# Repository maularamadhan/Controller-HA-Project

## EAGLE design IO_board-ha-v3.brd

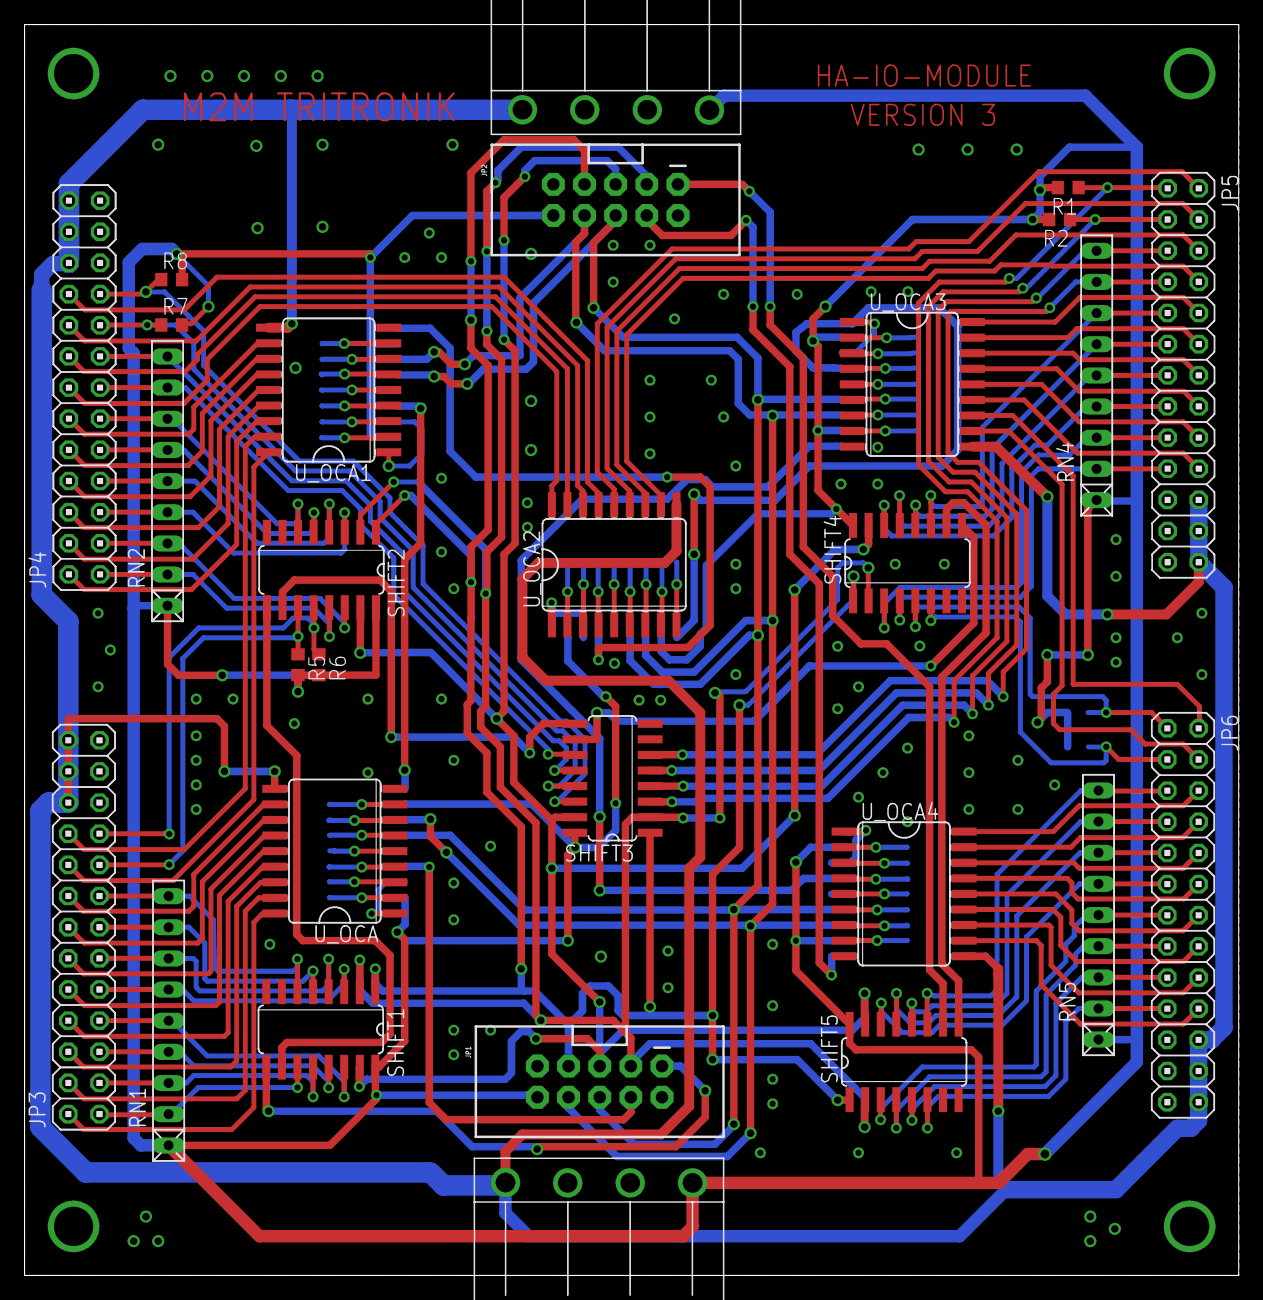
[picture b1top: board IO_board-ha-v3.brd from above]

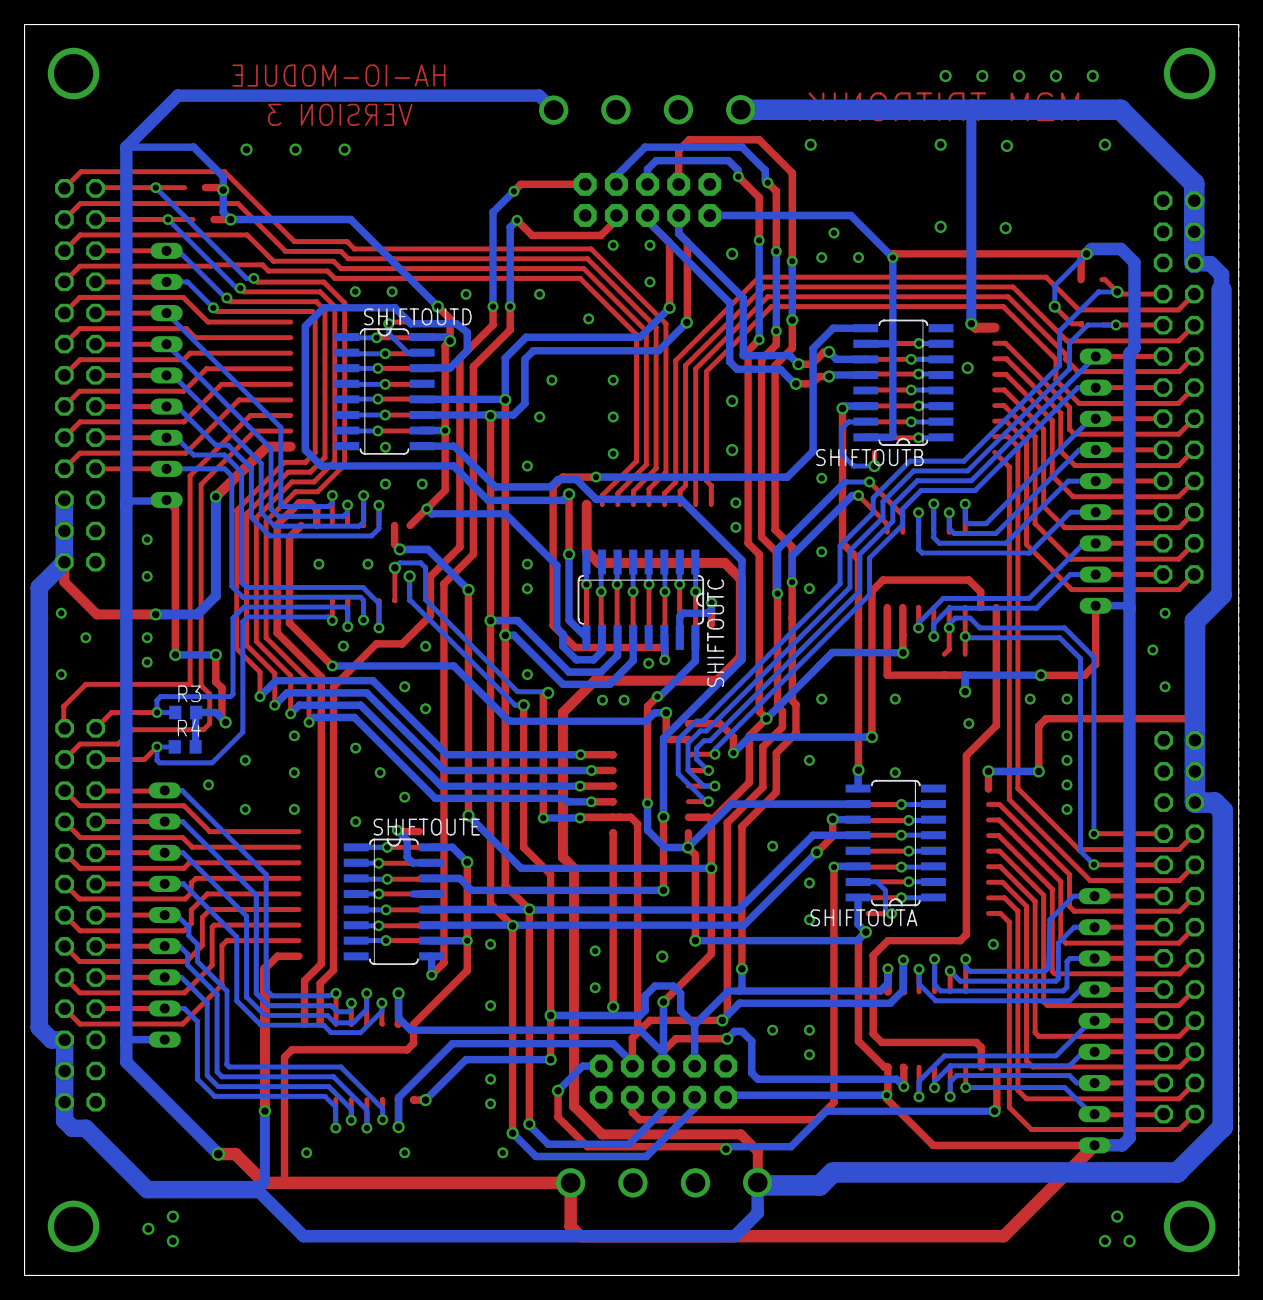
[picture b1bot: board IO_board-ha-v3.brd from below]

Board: 2 copper layers, 99.0 x 102.0 mm, 35 parts (7 on the bottom side), 140 nets.

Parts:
J1, J2: 4-PIN-CON-1759017
JP1, JP2: 2X5-SHROUDED
JP3, JP4, JP5, JP6: 2X13
R1, R2, R3, R4, R5, R6, R7, R8: 10K; R0603
RN1, RN2, RN4, RN5: 10K; RN-9
SHIFT1, SHIFT2, SHIFT3, SHIFT4, SHIFT5: 74HC165D; SO16
SHIFTOUTA: 74HC595D; SO16
SHIFTOUTB: 74HC595D; SO16
SHIFTOUTC: 74HC595D; SO16
SHIFTOUTD: 74HC595D; SO16
SHIFTOUTE: 74HC595D; SO16
U_OCA, U_OCA1, U_OCA2, U_OCA3, U_OCA4: ULN2803; SO18L

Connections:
1-1: JP3.1, RN1.2, SHIFT1.11
1-2: JP3.3, RN1.3, SHIFT1.12
1-3: JP3.5, RN1.4, SHIFT1.13
1-4: JP3.7, RN1.5, SHIFT1.14
1-5: JP3.9, RN1.6, SHIFT1.3
1-6: JP3.11, RN1.7, SHIFT1.4
1-7: JP3.13, RN1.8, SHIFT1.5
1-8: JP3.15, RN1.9, SHIFT1.6
2-1: JP3.17, R5.1, SHIFT2.11
2-2: JP3.19, R6.1, SHIFT2.12
2-3: JP4.1, RN2.2, SHIFT2.13
2-4: JP4.3, RN2.3, SHIFT2.14
2-5: JP4.5, RN2.4, SHIFT2.3
2-6: JP4.7, RN2.5, SHIFT2.4
2-7: JP4.9, RN2.6, SHIFT2.5
2-8: JP4.11, RN2.7, SHIFT2.6
3-1: JP4.13, RN2.8, SHIFT3.11
3-2: JP4.15, RN2.9, SHIFT3.12
3-3: JP4.17, R7.1, SHIFT3.13
3-4: JP4.19, R8.1, SHIFT3.14
3-5: JP5.1, R1.1, SHIFT3.3
3-6: JP5.3, R2.1, SHIFT3.4
3-7: JP5.5, RN4.9, SHIFT3.5
3-8: JP5.7, RN4.8, SHIFT3.6
4-1: JP5.9, RN4.7, SHIFT4.11
4-2: JP5.11, RN4.6, SHIFT4.12
4-3: JP5.13, RN4.5, SHIFT4.13
4-4: JP5.15, RN4.4, SHIFT4.14
4-5: JP5.17, RN4.3, SHIFT4.3
4-6: JP5.19, RN4.2, SHIFT4.4
4-7: JP6.1, R3.1, SHIFT4.5
4-8: JP6.3, R4.1, SHIFT4.6
5-1: JP6.5, RN5.9, SHIFT5.11
5-2: JP6.7, RN5.8, SHIFT5.12
5-3: JP6.9, RN5.7, SHIFT5.13
5-4: JP6.11, RN5.6, SHIFT5.14
5-5: JP6.13, RN5.5, SHIFT5.3
5-6: JP6.15, RN5.4, SHIFT5.4
5-7: JP6.17, RN5.3, SHIFT5.5
5-8: JP6.19, RN5.2, SHIFT5.6
+12V: J1.4, J2.1, JP3.22, JP3.24, JP3.26, JP4.22, JP4.24, JP4.26, JP5.22, JP5.24, JP5.26, JP6.22, JP6.24, JP6.26, U_OCA.10, U_OCA1.10, U_OCA2.10, U_OCA3.10, U_OCA4.10
A-1: SHIFTOUTA.15, U_OCA.1
A-2: SHIFTOUTA.1, U_OCA.2
A-3: SHIFTOUTA.2, U_OCA.3
A-4: SHIFTOUTA.3, U_OCA.4
A-5: SHIFTOUTA.4, U_OCA.5
A-6: SHIFTOUTA.5, U_OCA.6
A-7: SHIFTOUTA.6, U_OCA.7
A-8: SHIFTOUTA.7, U_OCA.8
B-1: SHIFTOUTB.15, U_OCA1.1
B-2: SHIFTOUTB.1, U_OCA1.2
B-3: SHIFTOUTB.2, U_OCA1.3
B-4: SHIFTOUTB.3, U_OCA1.4
B-5: SHIFTOUTB.4, U_OCA1.5
B-6: SHIFTOUTB.5, U_OCA1.6
B-7: SHIFTOUTB.6, U_OCA1.7
B-8: SHIFTOUTB.7, U_OCA1.8
C-1: SHIFTOUTC.15, U_OCA2.1
C-2: SHIFTOUTC.1, U_OCA2.2
C-3: SHIFTOUTC.2, U_OCA2.3
C-4: SHIFTOUTC.3, U_OCA2.4
C-5: SHIFTOUTC.4, U_OCA2.5
C-6: SHIFTOUTC.5, U_OCA2.6
C-7: SHIFTOUTC.6, U_OCA2.7
C-8: SHIFTOUTC.7, U_OCA2.8
CE: JP1.5, JP2.5, SHIFT1.15, SHIFT2.15, SHIFT3.15, SHIFT4.15, SHIFT5.15
CLK: JP1.3, JP2.3, SHIFT1.2, SHIFT2.2, SHIFT3.2, SHIFT4.2, SHIFT5.2
D-1: SHIFTOUTD.15, U_OCA3.1
D-2: SHIFTOUTD.1, U_OCA3.2
D-3: SHIFTOUTD.2, U_OCA3.3
D-4: SHIFTOUTD.3, U_OCA3.4
D-5: SHIFTOUTD.4, U_OCA3.5
D-6: SHIFTOUTD.5, U_OCA3.6
D-7: SHIFTOUTD.6, U_OCA3.7
D-8: SHIFTOUTD.7, U_OCA3.8
E-1: SHIFTOUTE.15, U_OCA4.1
E-2: SHIFTOUTE.1, U_OCA4.2
E-3: SHIFTOUTE.2, U_OCA4.3
E-4: SHIFTOUTE.3, U_OCA4.4
E-5: SHIFTOUTE.4, U_OCA4.5
E-6: SHIFTOUTE.5, U_OCA4.6
E-7: SHIFTOUTE.6, U_OCA4.7
E-8: SHIFTOUTE.7, U_OCA4.8
GND: J1.2, J1.3, J2.2, J2.3, JP1.2, JP1.9, JP2.2, JP2.9, JP3.21, JP3.23, JP3.25, JP4.21, JP4.23, JP4.25, JP5.21, JP5.23, JP5.25, JP6.21, JP6.23, JP6.25, SHIFT1.8, SHIFT2.8, SHIFT3.8, SHIFT4.8, SHIFT5.8, SHIFTOUTA.8, SHIFTOUTA.13, SHIFTOUTB.8, SHIFTOUTB.13, SHIFTOUTC.8, SHIFTOUTC.13, SHIFTOUTD.8, SHIFTOUTD.13, SHIFTOUTE.8, SHIFTOUTE.13, U_OCA.9, U_OCA1.9, U_OCA2.9, U_OCA3.9, U_OCA4.9
unnamed: SHIFT2.10, SHIFT3.9
unnamed: SHIFT3.10, SHIFT4.9
unnamed: SHIFT4.10, SHIFT5.9
unnamed: SHIFTOUTA.9, SHIFTOUTB.14
unnamed: SHIFTOUTC.9, SHIFTOUTD.14
unnamed: SHIFTOUTB.9, SHIFTOUTC.14
unnamed: SHIFTOUTD.9, SHIFTOUTE.14
unnamed: SHIFT1.10, SHIFT2.9
OUTA1: JP3.2, U_OCA.18
OUTA2: JP3.4, U_OCA.17
OUTA3: JP3.6, U_OCA.16
OUTA4: JP3.8, U_OCA.15
OUTA5: JP3.10, U_OCA.14
OUTA6: JP3.12, U_OCA.13
OUTA7: JP3.14, U_OCA.12
OUTA8: JP3.16, U_OCA.11
OUTB1: JP3.18, U_OCA1.18
OUTB2: JP3.20, U_OCA1.17
OUTB3: JP4.2, U_OCA1.16
OUTB4: JP4.4, U_OCA1.15
OUTB5: JP4.6, U_OCA1.14
OUTB6: JP4.8, U_OCA1.13
OUTB7: JP4.10, U_OCA1.12
OUTB8: JP4.12, U_OCA1.11
OUTC1: JP4.14, U_OCA2.18
OUTC2: JP4.16, U_OCA2.17
OUTC3: JP4.18, U_OCA2.16
OUTC4: JP4.20, U_OCA2.15
OUTC5: JP5.2, U_OCA2.14
OUTC6: JP5.4, U_OCA2.13
OUTC7: JP5.6, U_OCA2.12
OUTC8: JP5.8, U_OCA2.11
OUTD1: JP5.10, U_OCA3.18
OUTD2: JP5.12, U_OCA3.17
OUTD3: JP5.14, U_OCA3.16
OUTD4: JP5.16, U_OCA3.15
OUTD5: JP5.18, U_OCA3.14
OUTD6: JP5.20, U_OCA3.13
OUTD7: JP6.2, U_OCA3.12
OUTD8: JP6.4, U_OCA3.11
OUTE1: JP6.6, U_OCA4.18
OUTE2: JP6.8, U_OCA4.17
OUTE3: JP6.10, U_OCA4.16
OUTE4: JP6.12, U_OCA4.15
OUTE5: JP6.14, U_OCA4.14
OUTE6: JP6.16, U_OCA4.13
OUTE7: JP6.18, U_OCA4.12
OUTE8: JP6.20, U_OCA4.11
PL: JP1.7, JP2.7, SHIFT1.1, SHIFT2.1, SHIFT3.1, SHIFT4.1, SHIFT5.1
Q7: JP1.1, SHIFT1.9
Q7_2: JP2.1, SHIFT5.10
SHCP: JP1.8, JP2.8, SHIFTOUTA.11, SHIFTOUTB.11, SHIFTOUTC.11, SHIFTOUTD.11, SHIFTOUTE.11
SR_DS: JP1.4, SHIFTOUTA.14
SR_DS_2: JP2.4, SHIFTOUTE.9
STCP: JP1.6, JP2.6, SHIFTOUTA.12, SHIFTOUTB.12, SHIFTOUTC.12, SHIFTOUTD.12, SHIFTOUTE.12
VCC: J1.1, J2.4, JP1.10, JP2.10, R1.2, R2.2, R3.2, R4.2, R5.2, R6.2, R7.2, R8.2, RN1.1, RN2.1, RN4.1, RN5.1, SHIFT1.16, SHIFT2.16, SHIFT3.16, SHIFT4.16, SHIFT5.16, SHIFTOUTA.10, SHIFTOUTA.16, SHIFTOUTB.10, SHIFTOUTB.16, SHIFTOUTC.10, SHIFTOUTC.16, SHIFTOUTD.10, SHIFTOUTD.16, SHIFTOUTE.10, SHIFTOUTE.16

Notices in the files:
parts and their libraries:
SparkFun-Connectors: Licensing: Creative Commons ShareAlike 4.0 International - https://creativecommons.org/licenses/by-sa/4.0
SparkFun: Licensing: CC v3.0 Share-Alike You are welcome to use this library for commercial purposes.
